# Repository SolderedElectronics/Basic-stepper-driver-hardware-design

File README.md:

# Basic stepper driver Hardware design

## About the product

|  |
| :----------------------------------------------------------: |
|      [Buy Basic stepper driver](https://www.solde.red/333134)      |

This driver for stepper motor enables control over a stepper motor that does not require more than 800mA of current and works at up to 14V voltage. Except for the driver, it has built-in LED lights that indicate which phase of the motor is currently active. Connecting with microcontroller is easy, and control is directly through the library.

## Repository contents

All Soldered Electronics hardware designed in KiCAD, and repositories are organized in the following way:

- CAD folder - contains KiCAD files (Schematics, Board, Panel Board), sorted by version. Change log lists all changes between versions.
- OUTPUTS - contains useful files, such as Bill of Materials (BOM), PDF of schematics, 3D .step file of the board and gerber files, sorted by version. 
- OUTPUTS -> Compliance - Certificates and useful legal stuff. 

## Want to contribute?

Please feel free to submit a pull request if you have any contributions. We encourage you to submit an issue or pull request if you find a bug. 

## About Soldered

At Soldered, we design and manufacture a wide selection of electronic products to help you turn your ideas into acts and bring you one step closer to your final project. Our products are intented for makers and crafted in-house by our experienced team in Osijek, Croatia. We believe that sharing is a crucial element for improvement and innovation, and we work hard to stay connected with all our makers regardless of their skill or experience level. Therefore, all our products are open-source. Finally, we always have your back. If you face any problem concerning either your shopping experience or your electronics project, our team will help you deal with it, offering efficient customer service and cost-free technical support anytime. Some of those might be useful for you:

- [Web Store](https://www.soldered.com/shop)
- [Tutorials & Projects](https://soldered.com/learn)
- [Community & Technical support](https://soldered.com/community)

## License info

All Soldered open-source hardware (OSH) is under The TAPR Open Hardware License. Read more in the LICENSE file. 

No warranty - all designs in this repository are distributed in the hope that they will be useful, but without any warranty. They are provided "AS IS", therefore without warranty of any kind, either expressed or implied. The entire quality and performance of what you do with the contents of this repository are your responsibility. In no event, Soldered Electronics will be liable for your damages, losses, including any general, special, incidental or consequential damage arising out of the use or inability to use the contents of this repository. 

## Have fun! 
And thank you from your fellow makers at Soldered Electronics.

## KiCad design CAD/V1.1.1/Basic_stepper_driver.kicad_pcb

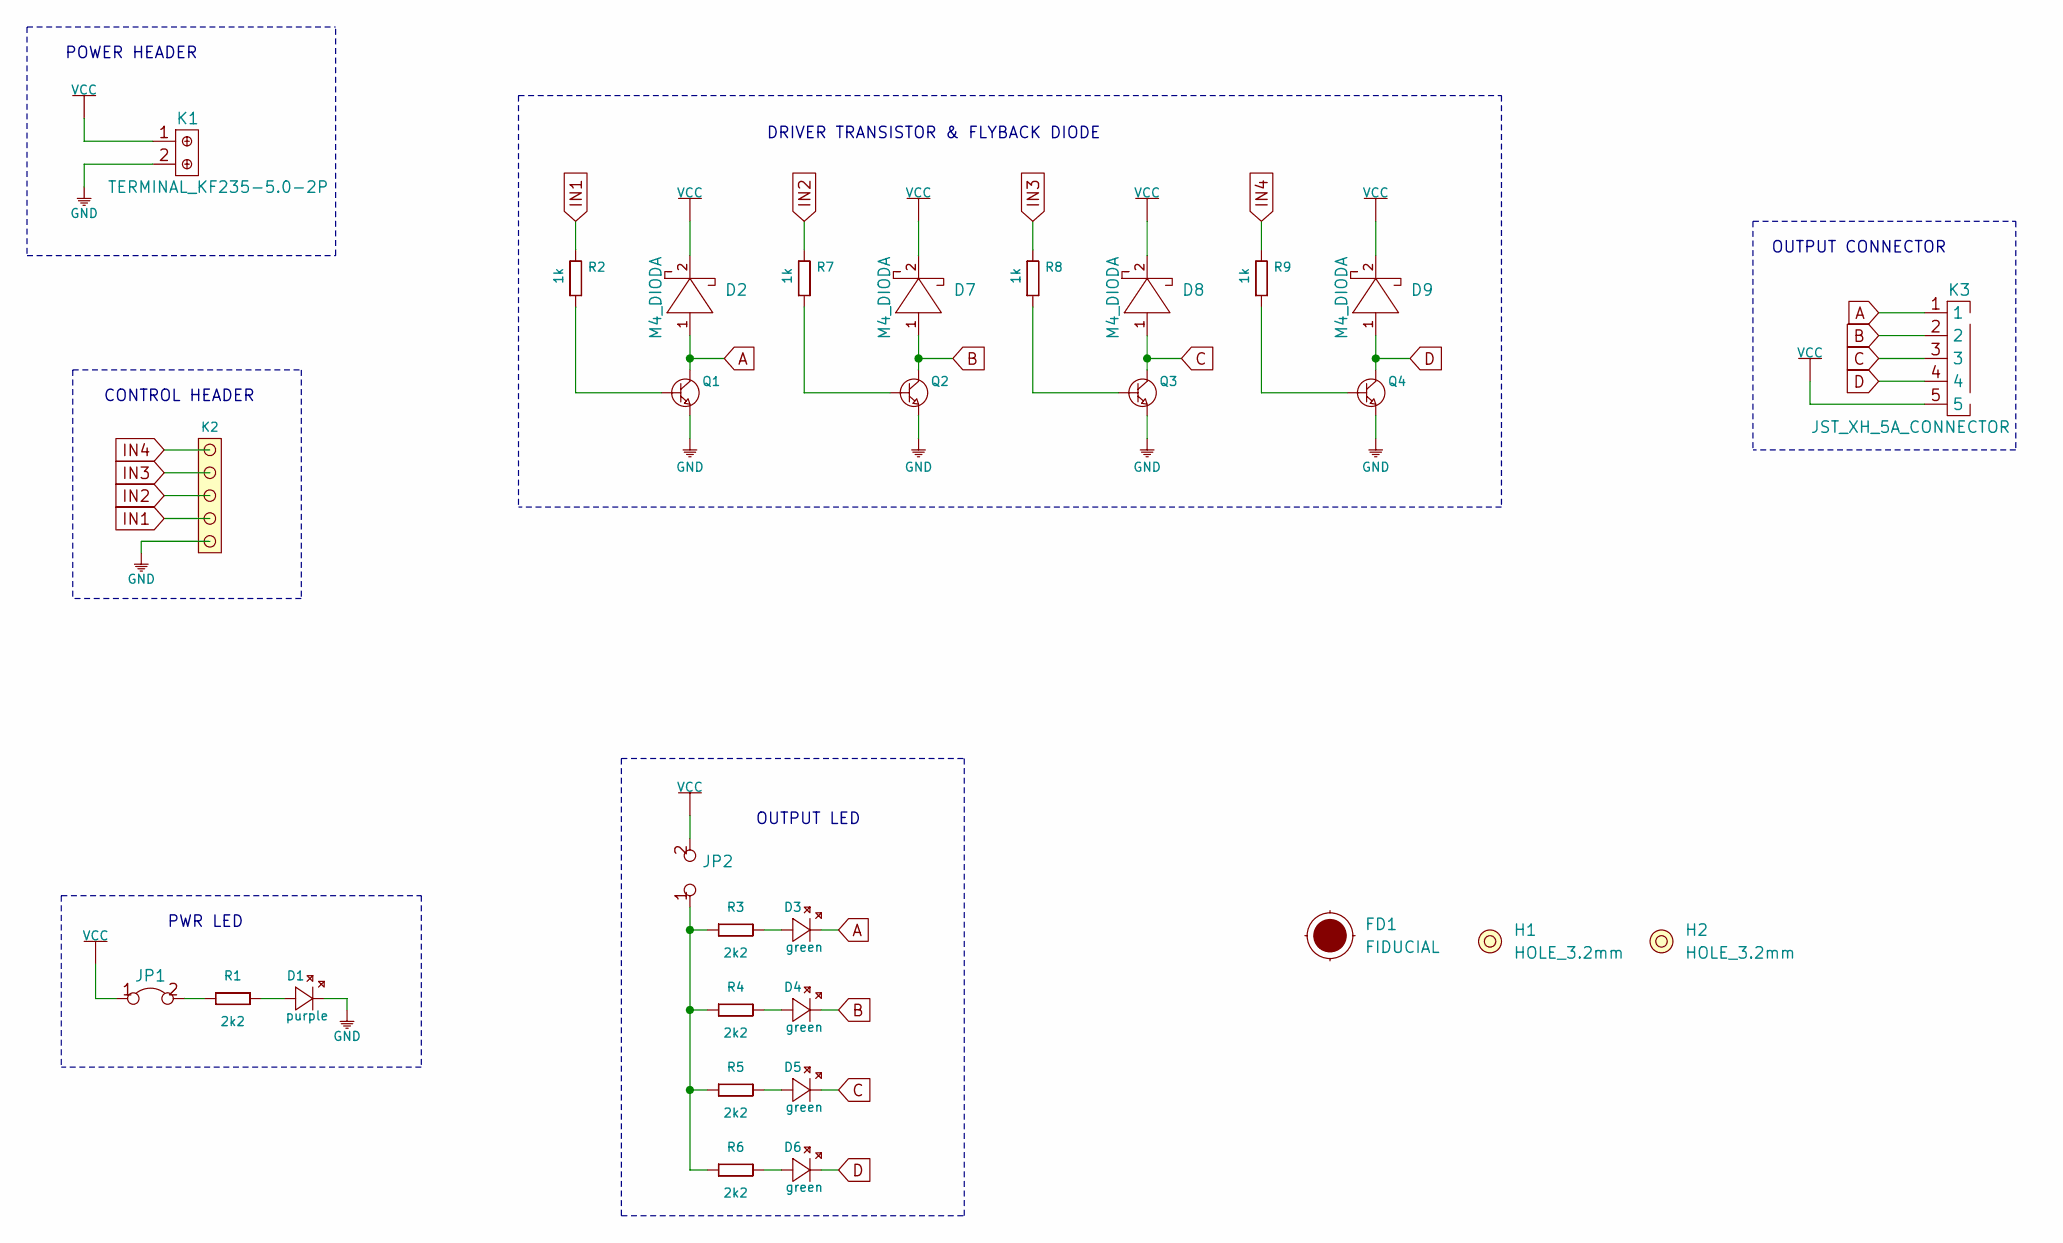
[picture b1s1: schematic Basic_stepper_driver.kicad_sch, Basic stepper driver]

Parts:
D1: purple; 0402LED
D2, D7, D8, D9: M4_DIODA
D3, D4, D5, D6: green; 0402LED
FD1: FIDUCIAL; FIDUCIAL_23
H1, H2: HOLE_3.2mm
JP1: SMD-JUMPER-CONNECTED_TRACE_SLODERMASK
JP2: SMD_JUMPER
K1: TERMINAL_KF235-5.0-2P
K2: HEADER_MALE_5X1
K3: JST_XH_5A_CONNECTOR
Q1, Q2, Q3, Q4: NPN; SOT-23-3
R1, R3, R4, R5, R6: 2k2; 0402R
R2, R7, R8, R9: 1k; 0603R

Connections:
A: D2.1 (A), D3.2 (K), K3.1, Q1.3 (C)
B: D4.2 (K), D7.1 (A), K3.2, Q2.3 (C)
C: D5.2 (K), D8.1 (A), K3.3, Q3.3 (C)
D: D6.2 (K), D9.1 (A), K3.4, Q4.3 (C)
GND: D1.2 (K), K1.2, K2.1, Q1.2 (E), Q2.2 (E), Q3.2 (E), Q4.2 (E)
IN1: K2.2, R2.2
IN2: K2.3, R7.2
IN3: K2.4, R8.2
IN4: K2.5, R9.2
unnamed: D1.1 (A), R1.2
unnamed: D3.1 (A), R3.2
unnamed: D4.1 (A), R4.2
unnamed: D5.1 (A), R5.2
unnamed: D6.1 (A), R6.2
unnamed: JP2.1, R3.1, R4.1, R5.1, R6.1
unnamed: Q1.1 (B), R2.1
unnamed: Q2.1 (B), R7.1
unnamed: Q3.1 (B), R8.1
unnamed: Q4.1 (B), R9.1
unnamed: JP1.2, R1.1
VCC: D2.2 (K), D7.2 (K), D8.2 (K), D9.2 (K), JP1.1, JP2.2, K1.1, K3.5

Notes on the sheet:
CONTROL HEADER
OUTPUT LED
POWER HEADER
OUTPUT CONNECTOR
PWR LED
DRIVER TRANSISTOR & FLYBACK DIODE

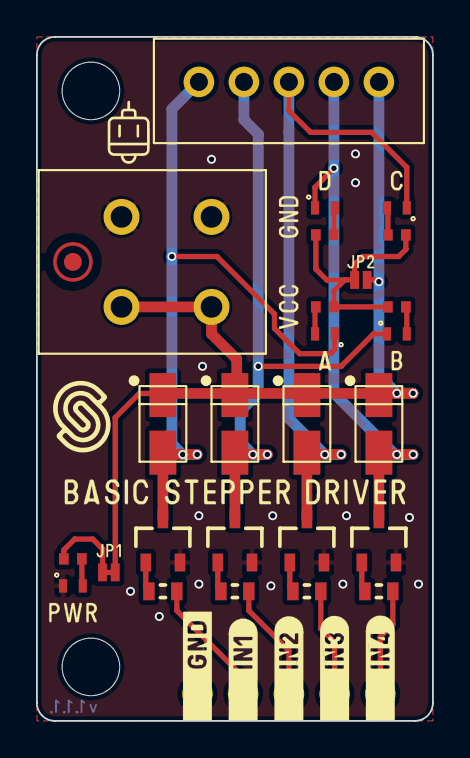
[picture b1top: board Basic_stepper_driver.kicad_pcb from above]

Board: 2 copper layers, 22.0 x 38.0 mm, 30 parts (1 on the bottom side), 21 nets.

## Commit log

2022-08-06 Updating open source files.
